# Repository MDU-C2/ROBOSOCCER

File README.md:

Multi-robot Soccer - RoboCup
=======================

About
-----------------------
Welcome to the DVA490 and DVA474 Project Course, project name Multi-robot Soccer - RoboCup. 
The project is about creating SSL RoboCup (Division B) robots and developing the accompanying software.

Roadmap
-----------------------
Hardware:
- [ ] Hardware mechanical design
- [ ] Hardware 3D design
- [ ] Hardware circuit/electrical design

Software:
- [x] Simulation Interface
- [x] SSL Interface
- [ ] Hardware Interface
- [ ] Communication protocol
- [ ] Raspberry Pi executable (Individual Robot Behaviour)
- [ ] Central computer executable (Collective Robot Behaviour)

Contributors and roles
-----------------------
This project was developed by:
- Mudar Ibrahim: Team leader and software developer
- Carl Larsson: Software lead and software developer
- Viktor Eriksson: Software developer
- Jacob Johansson: Software developer
- Aaiza Aziz Khan: Software developer
- Shruthi Puthiya Kunnon: Software developer
- Emil Åberg: Software developer
- Pontus Svensson: Hardware lead, hardware developer and software developer
- Anton Grusell: Hardware developer
- Johanna Melander: Hardware developer
- Fredrik Westerbom: Hardware developer and software developer

### Contact:
Carl Larsson: cln20001@student.mdu.se

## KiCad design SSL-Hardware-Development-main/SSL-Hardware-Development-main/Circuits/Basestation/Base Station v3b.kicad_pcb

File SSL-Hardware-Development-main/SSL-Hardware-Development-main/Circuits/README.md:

# Circuit Designs

This folder contains all circuitry and PCB design for the robot.

See [CONTRIBUTING.md](Documentation/CONTRIBUTING.md#Contributing-to-Hardware) 

## Changes
Update your changes here, include a description, file, name and commit number.

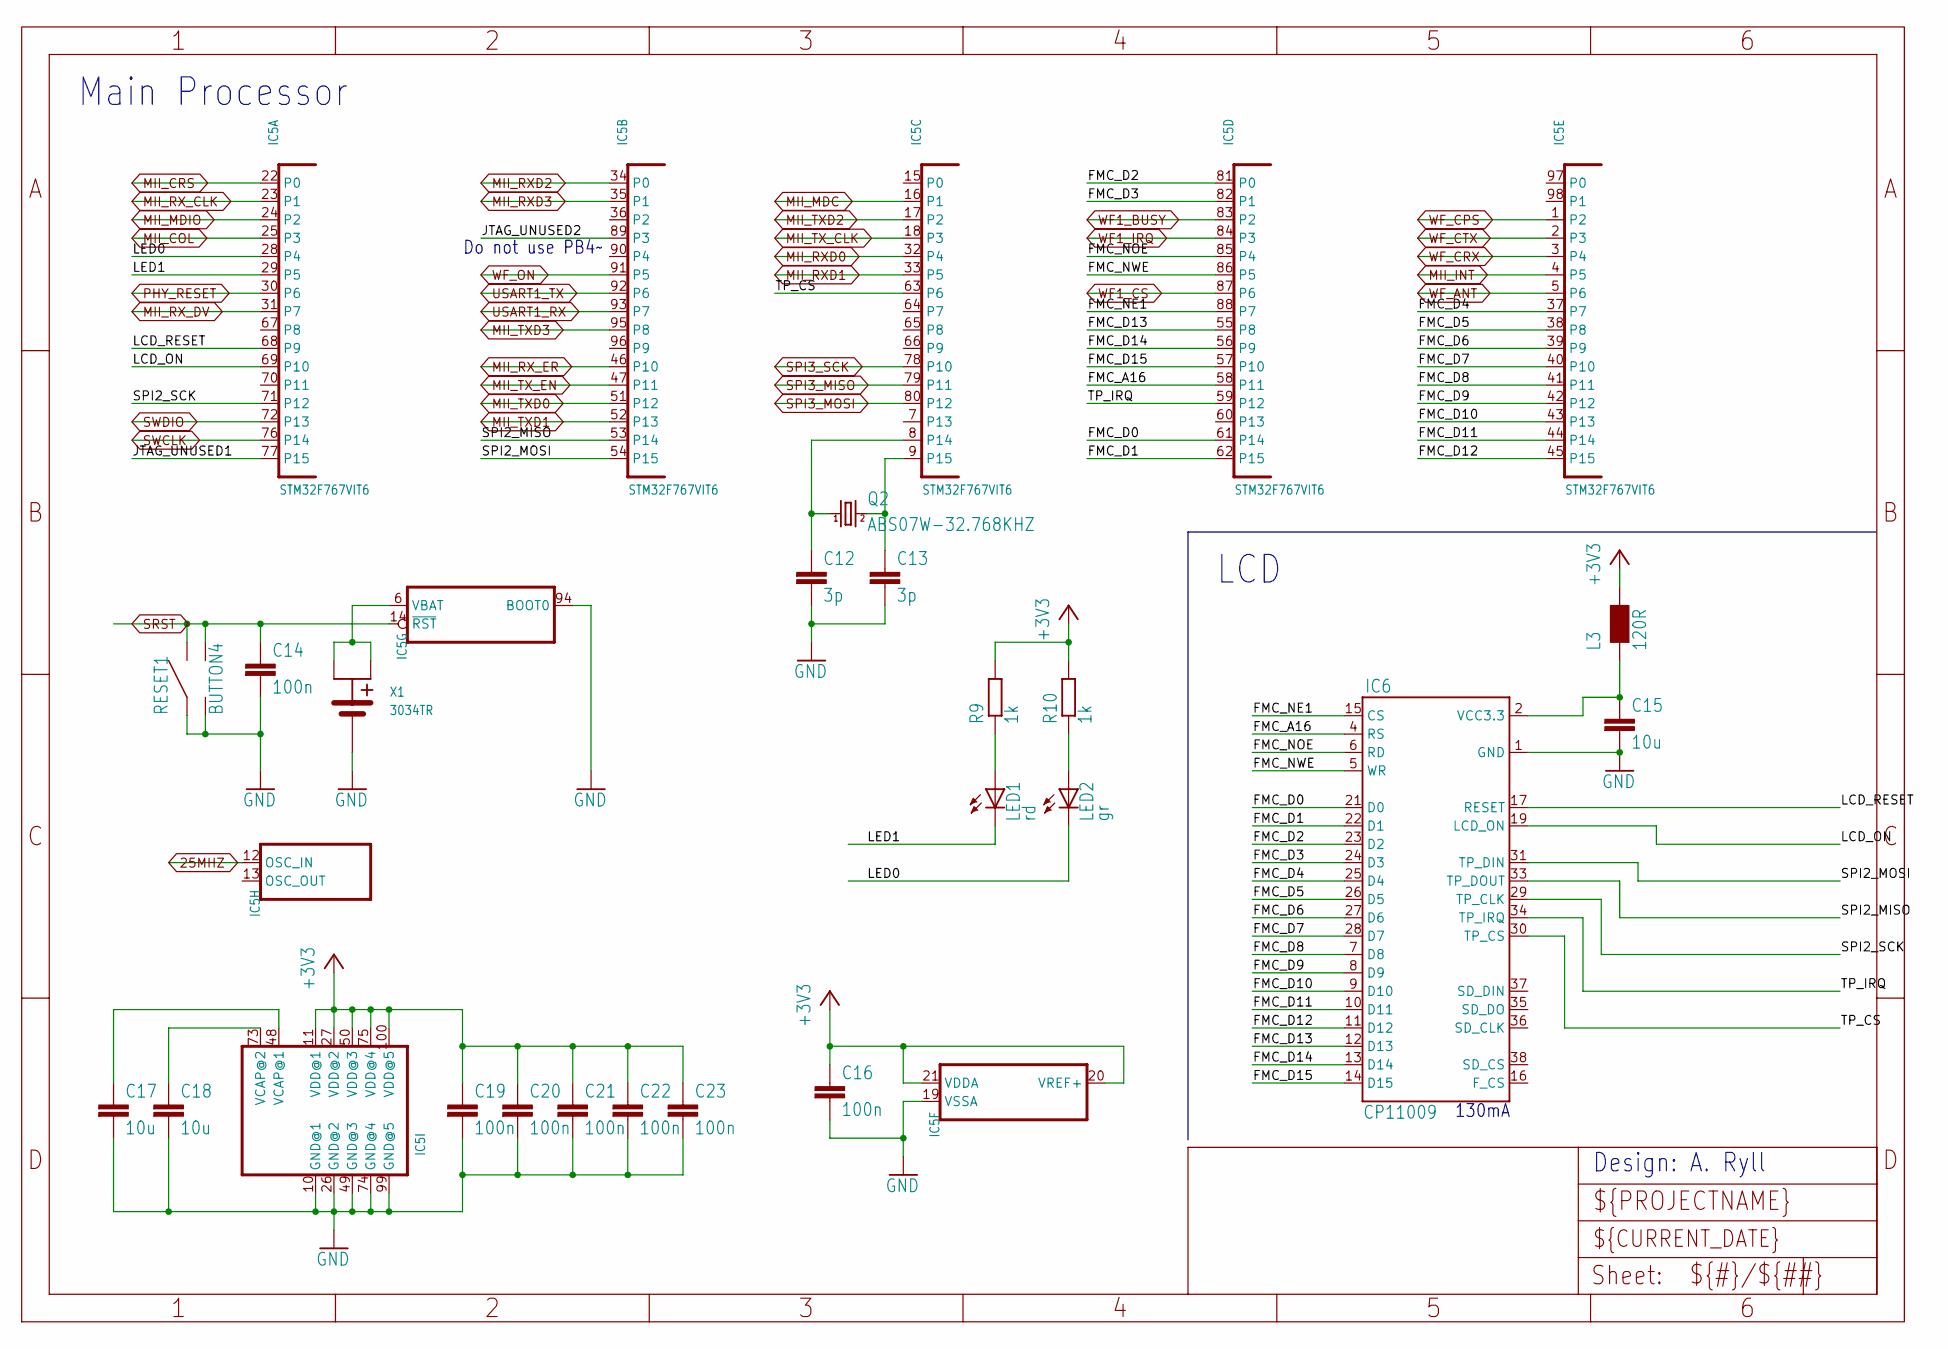
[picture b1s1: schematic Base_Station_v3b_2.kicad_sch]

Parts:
C12, C13: 3p; C0603
C14, C16, C19, C20, C21, C22, C23: 100n; C0603
C15, C17, C18: 10u; C0603
IC5: STM32F767VIT6; LQFP100-ST
IC6: CP11009; CP11009-THX
L3: 120R; 0603
LED1: rd; CHIP-LED0603
LED2: gr; CHIP-LED0603
Q2: ABS07W-32.768KHZ; CRYSTAL-07W
R9, R10: 1k; R0603
RESET1: BUTTON4
X1: 3034TR; CR2025

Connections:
25MHZ: IC5.12 (OSC_IN); also elsewhere on the board
+3V3: C16.1, C19.1, C20.1, C21.1, C22.1, C23.1, IC5.11 (VDD@1), IC5.20 (VREF+), IC5.21 (VDDA), IC5.27 (VDD@2), IC5.50 (VDD@3), IC5.75 (VDD@4), IC5.100 (VDD@5), L3.2, R9.2, R10.2; also elsewhere on the board
FMC_A16: IC5.58 (P11), IC6.4 (RS)
FMC_D0: IC5.61 (P14), IC6.21 (D0)
FMC_D1: IC5.62 (P15), IC6.22 (D1)
FMC_D2: IC5.81 (P0), IC6.23 (D2)
FMC_D3: IC5.82 (P1), IC6.24 (D3)
FMC_D4: IC5.37 (P7), IC6.25 (D4)
FMC_D5: IC5.38 (P8), IC6.26 (D5)
FMC_D6: IC5.39 (P9), IC6.27 (D6)
FMC_D7: IC5.40 (P10), IC6.28 (D7)
FMC_D8: IC5.41 (P11), IC6.7 (D8)
FMC_D9: IC5.42 (P12), IC6.8 (D9)
FMC_D10: IC5.43 (P13), IC6.9 (D10)
FMC_D11: IC5.44 (P14), IC6.10 (D11)
FMC_D12: IC5.45 (P15), IC6.11 (D12)
FMC_D13: IC5.55 (P8), IC6.12 (D13)
FMC_D14: IC5.56 (P9), IC6.13 (D14)
FMC_D15: IC5.57 (P10), IC6.14 (D15)
FMC_NE1: IC5.88 (P7), IC6.15 (CS)
FMC_NOE: IC5.85 (P4), IC6.6 (RD)
FMC_NWE: IC5.86 (P5), IC6.5 (WR)
GND: C12.2, C13.2, C14.2, C15.2, C16.2, C17.2, C18.2, C19.2, C20.2, C21.2, C22.2, C23.2, IC5.10 (GND@1), IC5.19 (VSSA), IC5.26 (GND@2), IC5.49 (GND@3), IC5.74 (GND@4), IC5.94 (BOOT0), IC5.99 (GND@5), IC6.1 (GND), RESET1.1, RESET1.2, X1.GND; also elsewhere on the board
JTAG_UNUSED1: IC5.77 (P15)
JTAG_UNUSED2: IC5.89 (P3)
LCD_ON: IC5.69 (P10), IC6.19 (LCD_ON)
LCD_RESET: IC5.68 (P9), IC6.17 (RESET)
LED0: IC5.28 (P4), LED2.C
LED1: IC5.29 (P5), LED1.C
MII_COL: IC5.25 (P3); also elsewhere on the board
MII_CRS: IC5.22 (P0); also elsewhere on the board
MII_INT: IC5.4 (P5); also elsewhere on the board
MII_MDC: IC5.16 (P1); also elsewhere on the board
MII_MDIO: IC5.24 (P2); also elsewhere on the board
MII_RXD0: IC5.32 (P4); also elsewhere on the board
MII_RXD1: IC5.33 (P5); also elsewhere on the board
MII_RXD2: IC5.34 (P0); also elsewhere on the board
MII_RXD3: IC5.35 (P1); also elsewhere on the board
MII_RX_CLK: IC5.23 (P1); also elsewhere on the board
MII_RX_DV: IC5.31 (P7); also elsewhere on the board
MII_RX_ER: IC5.46 (P10); also elsewhere on the board
MII_TXD0: IC5.51 (P12); also elsewhere on the board
MII_TXD1: IC5.52 (P13); also elsewhere on the board
MII_TXD2: IC5.17 (P2); also elsewhere on the board
MII_TXD3: IC5.95 (P8); also elsewhere on the board
MII_TX_CLK: IC5.18 (P3); also elsewhere on the board
MII_TX_EN: IC5.47 (P11); also elsewhere on the board
unnamed: C18.1, IC5.73 (VCAP@2)
unnamed: C17.1, IC5.48 (VCAP@1)
unnamed: LED2.A, R10.1
unnamed: LED1.A, R9.1
unnamed: C15.1, IC6.2 (VCC3.3), L3.1
OSC32_IN: C12.1, IC5.8 (P14), Q2.1
OSC32_OUT: C13.1, IC5.9 (P15), Q2.2
PHY_RESET: IC5.30 (P6); also elsewhere on the board
SPI2_MISO: IC5.53 (P14), IC6.33 (TP_DOUT)
SPI2_MOSI: IC5.54 (P15), IC6.31 (TP_DIN)
SPI2_SCK: IC5.71 (P12), IC6.29 (TP_CLK)
SPI3_MISO: IC5.79 (P11); also elsewhere on the board
SPI3_MOSI: IC5.80 (P12); also elsewhere on the board
SPI3_SCK: IC5.78 (P10); also elsewhere on the board
SRST: C14.1, IC5.14 (~RST), RESET1.3, RESET1.4; also elsewhere on the board
SWCLK: IC5.76 (P14); also elsewhere on the board
SWDIO: IC5.72 (P13); also elsewhere on the board
TP_CS: IC5.63 (P6), IC6.30 (TP_CS)
TP_IRQ: IC5.59 (P12), IC6.34 (TP_IRQ)
USART1_RX: IC5.93 (P7); also elsewhere on the board
USART1_TX: IC5.92 (P6); also elsewhere on the board
VBAT: IC5.6 (VBAT), X1.POS1, X1.POS2
WF1_BUSY: IC5.83 (P2); also elsewhere on the board
WF1_CS: IC5.87 (P6); also elsewhere on the board
WF1_IRQ: IC5.84 (P3); also elsewhere on the board
WF_ANT: IC5.5 (P6); also elsewhere on the board
WF_CPS: IC5.1 (P2); also elsewhere on the board
WF_CRX: IC5.3 (P4); also elsewhere on the board
WF_CTX: IC5.2 (P3); also elsewhere on the board
WF_ON: IC5.91 (P5); also elsewhere on the board

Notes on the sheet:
130mA
LCD
Main Processor
Design: A. Ryll
Do not use PB4~~{}

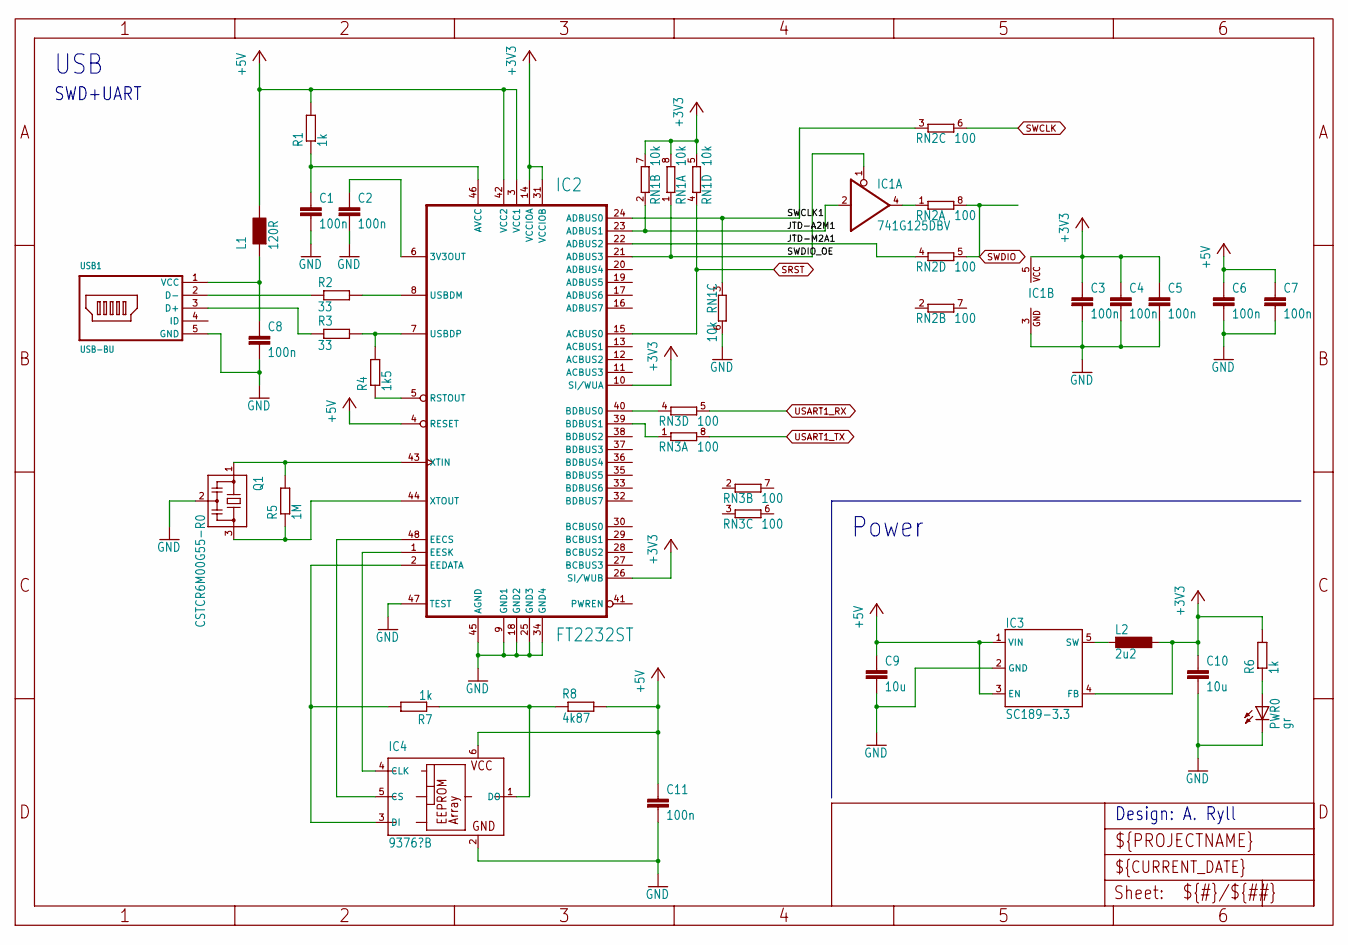
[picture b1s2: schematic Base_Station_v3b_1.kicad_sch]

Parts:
C1, C2, C3, C4, C5, C6, C7, C8, C11: 100n; C0603
C9, C10: 10u; C0603
IC1: 741G125DBV; SOT23-5
IC2: FT2232ST; LQFP48-ST
IC3: SC189-3.3; SOT23-5
IC4: 9376?B; SOT23-6
L1: 120R; 0603
L2: 2u2; IHLP1616
PWR0: gr; CHIP-LED0603
Q1: CSTCR6M00G55-R0; CSTCR6M
R1, R6, R7: 1k; R0603
R2, R3: 33; R0603
R4: 1k5; R0603
R5: 1M; R0603
R8: 4k87; R0603
RN1: 10k; EXB28V
RN2, RN3: 100; EXB28V
USB1: USB-BU; USB-BMICRO

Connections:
+3V3: C3.1, C4.1, C5.1, C10.1, IC1.5 (VCC), IC2.10 (SI/WUA), IC2.14 (VCCIOA), IC2.26 (SI/WUB), IC2.31 (VCCIOB), IC3.4 (FB), L2.P$1 (1), R6.2, RN1.5 (2), RN1.7 (2), RN1.8 (2); also elsewhere on the board
+5V: C6.1, C7.1, C9.1, C11.1, IC2.3 (VCC1), IC2.4 (RESET), IC2.42 (VCC2), IC3.1 (VIN), IC3.3 (EN), IC4.6 (VCC), L1.2, R1.2, R8.2; also elsewhere on the board
GND: C1.2, C2.2, C3.2, C4.2, C5.2, C6.2, C7.2, C8.2, C9.2, C10.2, C11.2, IC1.3 (GND), IC2.9 (GND1), IC2.18 (GND2), IC2.25 (GND3), IC2.34 (GND4), IC2.45 (AGND), IC2.47 (TEST), IC3.2 (GND), IC4.2 (GND), PWR0.C, Q1.2, RN1.6 (2), USB1.5 (GND); also elsewhere on the board
JTD-A2M1: IC1.2 (I), IC2.23 (ADBUS1), RN1.2 (1)
JTD-M2A1: IC2.22 (ADBUS2), RN2.4 (1)
unnamed: IC2.48 (EECS), IC4.5 (CS)
unnamed: IC2.1 (EESK), IC4.4 (CLK)
unnamed: IC2.2 (EEDATA), IC4.3 (DI), R7.2
unnamed: IC2.44 (XTOUT), Q1.3, R5.1
unnamed: IC4.1 (DO), R7.1, R8.1
unnamed: PWR0.A, R6.1
unnamed: IC1.4 (O), RN2.1
unnamed: IC2.40 (BDBUS0), RN3.4 (1)
unnamed: IC2.39 (BDBUS1), RN3.1
unnamed: IC2.7 (USBDP), R3.2, R4.2
unnamed: IC2.8 (USBDM), R2.2
unnamed: IC2.5 (RSTOUT), R4.1
unnamed: C2.1, IC2.6 (3V3OUT)
unnamed: C8.1, L1.1, USB1.1 (VCC)
unnamed: R2.1, USB1.2 (D-)
unnamed: R3.1, USB1.3 (D+)
unnamed: C1.1, IC2.46 (AVCC), R1.1
unnamed: IC2.43 (XTIN), Q1.1, R5.2
SRST: IC2.15 (ACBUS0), RN1.4 (1); also elsewhere on the board
SW-OUT: IC3.5 (SW), L2.P$2 (2)
SWCLK: RN2.6 (2); also elsewhere on the board
SWCLK1: IC2.24 (ADBUS0), RN1.3 (1), RN2.3 (1)
SWDIO: RN2.5 (2), RN2.8 (2); also elsewhere on the board
SWDIO_OE: IC1.1 (OE), IC2.21 (ADBUS3), RN1.1
USART1_RX: RN3.5 (2); also elsewhere on the board
USART1_TX: RN3.8 (2); also elsewhere on the board

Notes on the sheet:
Design: A. Ryll
USB
Power
SWD+UART

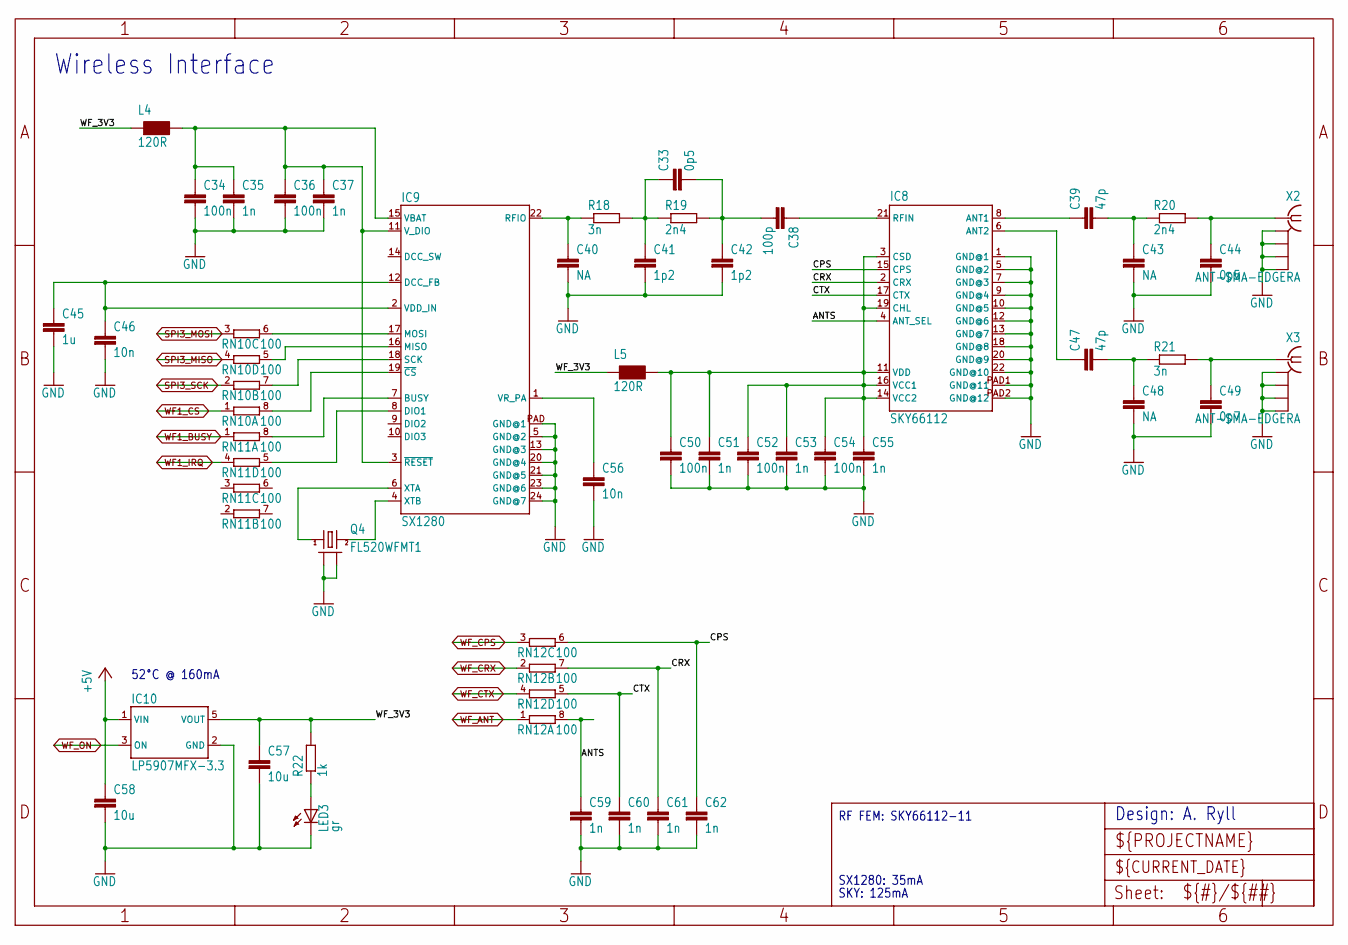
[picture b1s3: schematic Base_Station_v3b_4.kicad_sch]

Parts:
C33, C44: 0p5; C0402
C34, C36, C50, C52, C54: 100n; C0603
C35, C37, C51, C53, C55, C59, C60, C61, C62: 1n; C0603
C38: 100p; C0402
C39, C47: 47p; C0402
C40, C43, C48: NA; C0402
C41, C42: 1p2; C0402
C45: 1u; C0603
C46, C56: 10n; C0603
C49: 0p7; C0402
C57, C58: 10u; C0603
IC8: SKY66112; SMCM-22
IC9: SX1280; QFN24L
IC10: LP5907MFX-3.3; SOT23-5L
L4, L5: 120R; 0603
LED3: gr; CHIP-LED0603
Q4: FL520WFMT1; CRYSTAL-7M
R18, R21: 3n; R0402
R19, R20: 2n4; R0402
R22: 1k; R0603
RN10, RN11, RN12: 100; EXB28V
X2, X3: ANT-SMA-EDGERA; ANT-SMA-RA

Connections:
+5V: C58.1, IC10.1 (VIN); also elsewhere on the board
ANTS: C59.1, IC8.4 (ANT_SEL), RN12.8 (2)
CPS: C62.1, IC8.15 (CPS), RN12.6 (2)
CRX: C61.1, IC8.2 (CRX), RN12.7 (2)
CTX: C60.1, IC8.17 (CTX), RN12.5 (2)
GND: C34.2, C35.2, C36.2, C37.2, C40.2, C41.2, C42.2, C43.2, C44.2, C45.2, C46.2, C48.2, C49.2, C50.2, C51.2, C52.2, C53.2, C54.2, C55.2, C56.2, C57.2, C58.2, C59.2, C60.2, C61.2, C62.2, IC8.1 (GND@1), IC8.5 (GND@2), IC8.7 (GND@3), IC8.9 (GND@4), IC8.10 (GND@5), IC8.12 (GND@6), IC8.13 (GND@7), IC8.18 (GND@8), IC8.20 (GND@9), IC8.22 (GND@10), IC8.PAD1 (GND@11), IC8.PAD2 (GND@12), IC9.5 (GND@2), IC9.13 (GND@3), IC9.20 (GND@4), IC9.21 (GND@5), IC9.23 (GND@6), IC9.24 (GND@7), IC9.PAD (GND@1), IC10.2 (GND), LED3.C, Q4.2 (GND1), Q4.4 (GND2), X2.GND1 (GND), X2.GND2 (GND1), X2.GND3 (GND2), X2.GND4 (GND3), X3.GND1 (GND), X3.GND2 (GND1), X3.GND3 (GND2), X3.GND4 (GND3); also elsewhere on the board
unnamed: IC9.17 (MOSI), RN10.6 (2)
unnamed: IC9.16 (MISO), RN10.5 (2)
unnamed: IC9.18 (SCK), RN10.7 (2)
unnamed: IC9.19 (~CS), RN10.8 (2)
unnamed: IC9.7 (BUSY), RN11.8 (2)
unnamed: IC9.8 (DIO1), RN11.5 (2)
unnamed: LED3.A, R22.1
unnamed: IC9.6 (XTA), Q4.1
unnamed: IC9.4 (XTB), Q4.3 (2)
unnamed: C33.1, C41.1, R18.2, R19.1
unnamed: C33.2, C38.2, C42.1, R19.2
unnamed: C56.1, IC9.1 (VR_PA)
unnamed: C45.1, C46.1, IC9.2 (VDD_IN), IC9.12 (DCC_FB)
unnamed: C38.1, IC8.21 (RFIN)
unnamed: C39.2, C43.1, R20.1
unnamed: C44.1, R20.2, X2.C (1)
unnamed: C47.2, C48.1, R21.1
unnamed: C49.1, R21.2, X3.C (1)
unnamed: C39.1, IC8.8 (ANT1)
unnamed: C47.1, IC8.6 (ANT2)
RFIO1: C40.1, IC9.22 (RFIO), R18.1
SPI3_MISO: RN10.4 (1); also elsewhere on the board
SPI3_MOSI: RN10.3 (1); also elsewhere on the board
SPI3_SCK: RN10.2 (1); also elsewhere on the board
WF1_BUSY: RN11.1; also elsewhere on the board
WF1_CS: RN10.1; also elsewhere on the board
WF1_IRQ: RN11.4 (1); also elsewhere on the board
WF_3V3: C57.1, IC10.5 (VOUT), L4.1, L5.1, R22.2
WF_3V3FEM: C50.1, C51.1, C52.1, C53.1, C54.1, C55.1, IC8.3 (CSD), IC8.11 (VDD), IC8.14 (VCC2), IC8.16 (VCC1), IC8.19 (CHL), L5.2
WF_3V3SX: C34.1, C35.1, C36.1, C37.1, IC9.3 (~RESET), IC9.11 (V_DIO), IC9.15 (VBAT), L4.2
WF_ANT: RN12.1; also elsewhere on the board
WF_CPS: RN12.3 (1); also elsewhere on the board
WF_CRX: RN12.2 (1); also elsewhere on the board
WF_CTX: RN12.4 (1); also elsewhere on the board
WF_ON: IC10.3 (ON); also elsewhere on the board

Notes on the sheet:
SX1280: 35mA
52°C @ 160mA
Wireless Interface
RF FEM: SKY66112-11
SKY: 125mA
Design: A. Ryll

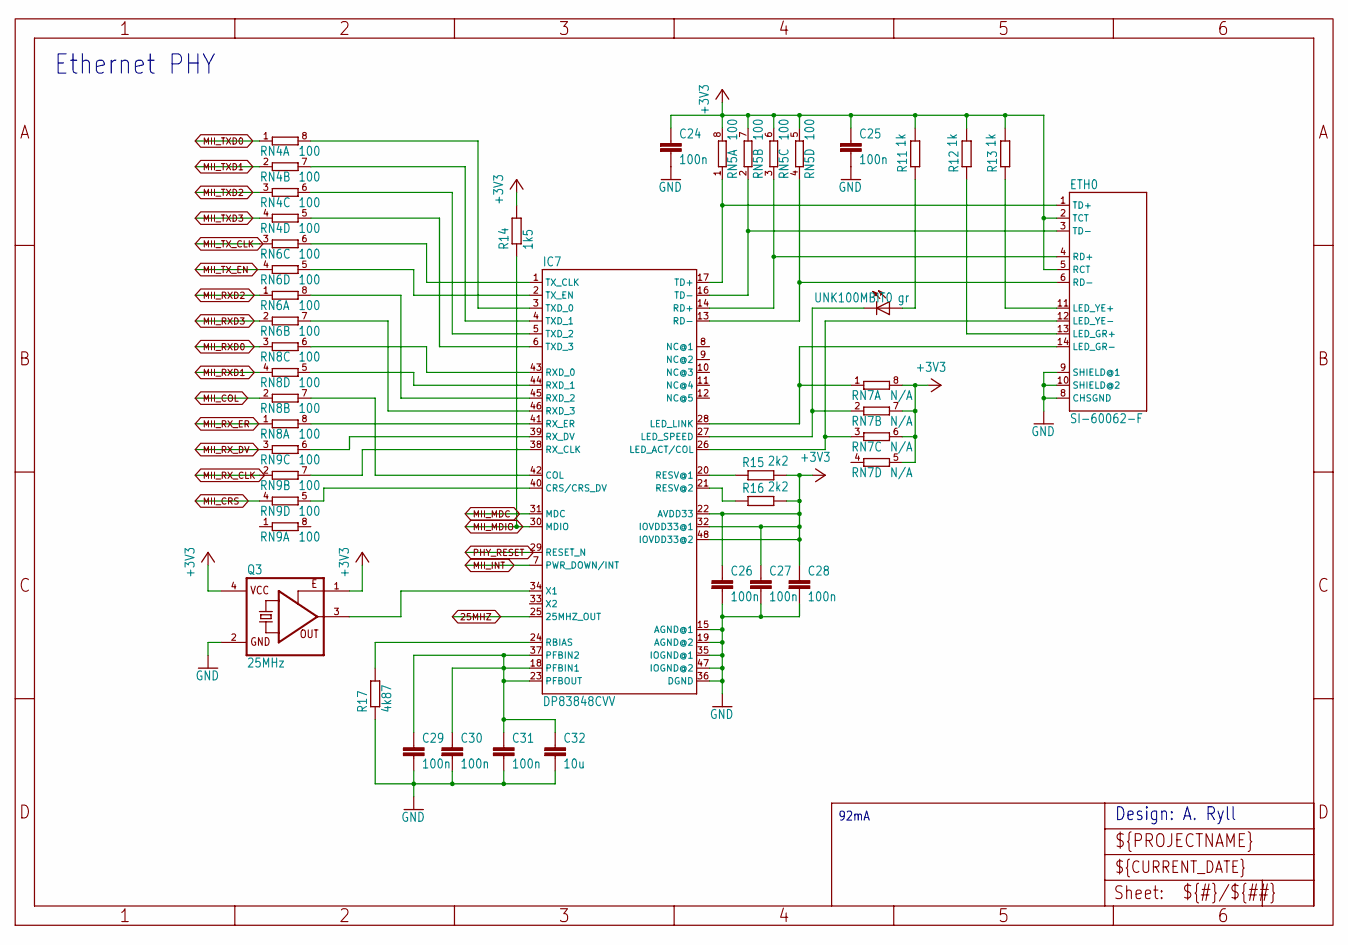
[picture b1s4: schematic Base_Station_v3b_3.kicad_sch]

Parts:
C24, C25, C26, C27, C28, C29, C30, C31: 100n; C0603
C32: 10u; C0603
ETH0: SI-60062-F; RJ45-LED
IC7: DP83848CVV; LQFP48
Q3: 25MHz; 7X
R11, R12, R13: 1k; R0603
R14: 1k5; R0603
R15, R16: 2k2; R0603
R17: 4k87; R0603
RN4, RN5, RN6, RN8, RN9: 100; EXB28V
RN7: N/A; EXB28V
UNK100MBIT0: gr; CHIP-LED0603

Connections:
25MHZ: IC7.25 (25MHZ_OUT); also elsewhere on the board
+3V3: C24.1, C25.1, C26.1, C27.1, C28.1, ETH0.2 (TCT), ETH0.5 (RCT), IC7.22 (AVDD33), IC7.32 (IOVDD33@1), IC7.48 (IOVDD33@2), Q3.1 (OE), Q3.4 (VCC), R11.2, R12.2, R13.2, R14.2, R15.2, R16.2, RN5.5 (2), RN5.6 (2), RN5.7 (2), RN5.8 (2), RN7.5 (2), RN7.6 (2), RN7.7 (2), RN7.8 (2); also elsewhere on the board
GND: C24.2, C25.2, C26.2, C27.2, C28.2, C29.2, C30.2, C31.2, C32.2, ETH0.8 (CHSGND), ETH0.9 (SHIELD@1), ETH0.10 (SHIELD@2), IC7.15 (AGND@1), IC7.19 (AGND@2), IC7.35 (IOGND@1), IC7.36 (DGND), IC7.47 (IOGND@2), Q3.2 (GND), R17.1; also elsewhere on the board
MII_COL: RN8.2 (1); also elsewhere on the board
MII_CRS: RN9.4 (1); also elsewhere on the board
MII_INT: IC7.7 (PWR_DOWN/INT); also elsewhere on the board
MII_MDC: IC7.31 (MDC); also elsewhere on the board
MII_MDIO: IC7.30 (MDIO), R14.1; also elsewhere on the board
MII_RXD0: RN8.3 (1); also elsewhere on the board
MII_RXD1: RN8.4 (1); also elsewhere on the board
MII_RXD2: RN6.1; also elsewhere on the board
MII_RXD3: RN6.2 (1); also elsewhere on the board
MII_RX_CLK: RN9.2 (1); also elsewhere on the board
MII_RX_DV: RN9.3 (1); also elsewhere on the board
MII_RX_ER: RN8.1; also elsewhere on the board
MII_TXD0: RN4.1; also elsewhere on the board
MII_TXD1: RN4.2 (1); also elsewhere on the board
MII_TXD2: RN4.3 (1); also elsewhere on the board
MII_TXD3: RN4.4 (1); also elsewhere on the board
MII_TX_CLK: RN6.3 (1); also elsewhere on the board
MII_TX_EN: RN6.4 (1); also elsewhere on the board
unnamed: IC7.3 (TXD_0), RN4.8 (2)
unnamed: IC7.4 (TXD_1), RN4.7 (2)
unnamed: IC7.5 (TXD_2), RN4.6 (2)
unnamed: IC7.6 (TXD_3), RN4.5 (2)
unnamed: IC7.1 (TX_CLK), RN6.6 (2)
unnamed: IC7.2 (TX_EN), RN6.5 (2)
unnamed: IC7.45 (RXD_2), RN6.8 (2)
unnamed: IC7.46 (RXD_3), RN6.7 (2)
unnamed: IC7.43 (RXD_0), RN8.6 (2)
unnamed: IC7.44 (RXD_1), RN8.5 (2)
unnamed: IC7.42 (COL), RN8.7 (2)
unnamed: IC7.41 (RX_ER), RN8.8 (2)
unnamed: IC7.39 (RX_DV), RN9.6 (2)
unnamed: IC7.38 (RX_CLK), RN9.7 (2)
unnamed: IC7.40 (CRS/CRS_DV), RN9.5 (2)
unnamed: IC7.24 (RBIAS), R17.2
unnamed: C29.1, C30.1, C31.1, C32.1, IC7.18 (PFBIN1), IC7.23 (PFBOUT), IC7.37 (PFBIN2)
unnamed: IC7.20 (RESV@1), R15.1
unnamed: IC7.21 (RESV@2), R16.1
unnamed: ETH0.12 (LED_YE-), IC7.26 (LED_ACT/COL), RN7.3 (1)
unnamed: IC7.27 (LED_SPEED), RN7.2 (1), UNK100MBIT0.C
unnamed: ETH0.14 (LED_GR-), IC7.28 (LED_LINK), RN7.1
unnamed: ETH0.6 (RD-), IC7.13 (RD-), RN5.4 (1)
unnamed: ETH0.4 (RD+), IC7.14 (RD+), RN5.3 (1)
unnamed: ETH0.3 (TD-), IC7.16 (TD-), RN5.2 (1)
unnamed: ETH0.1 (TD+), IC7.17 (TD+), RN5.1
unnamed: R11.1, UNK100MBIT0.A
unnamed: ETH0.13 (LED_GR+), R12.1
unnamed: ETH0.11 (LED_YE+), R13.1
unnamed: IC7.34 (X1), Q3.3 (FO)
PHY_RESET: IC7.29 (RESET_N); also elsewhere on the board

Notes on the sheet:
Ethernet PHY
92mA
Design: A. Ryll

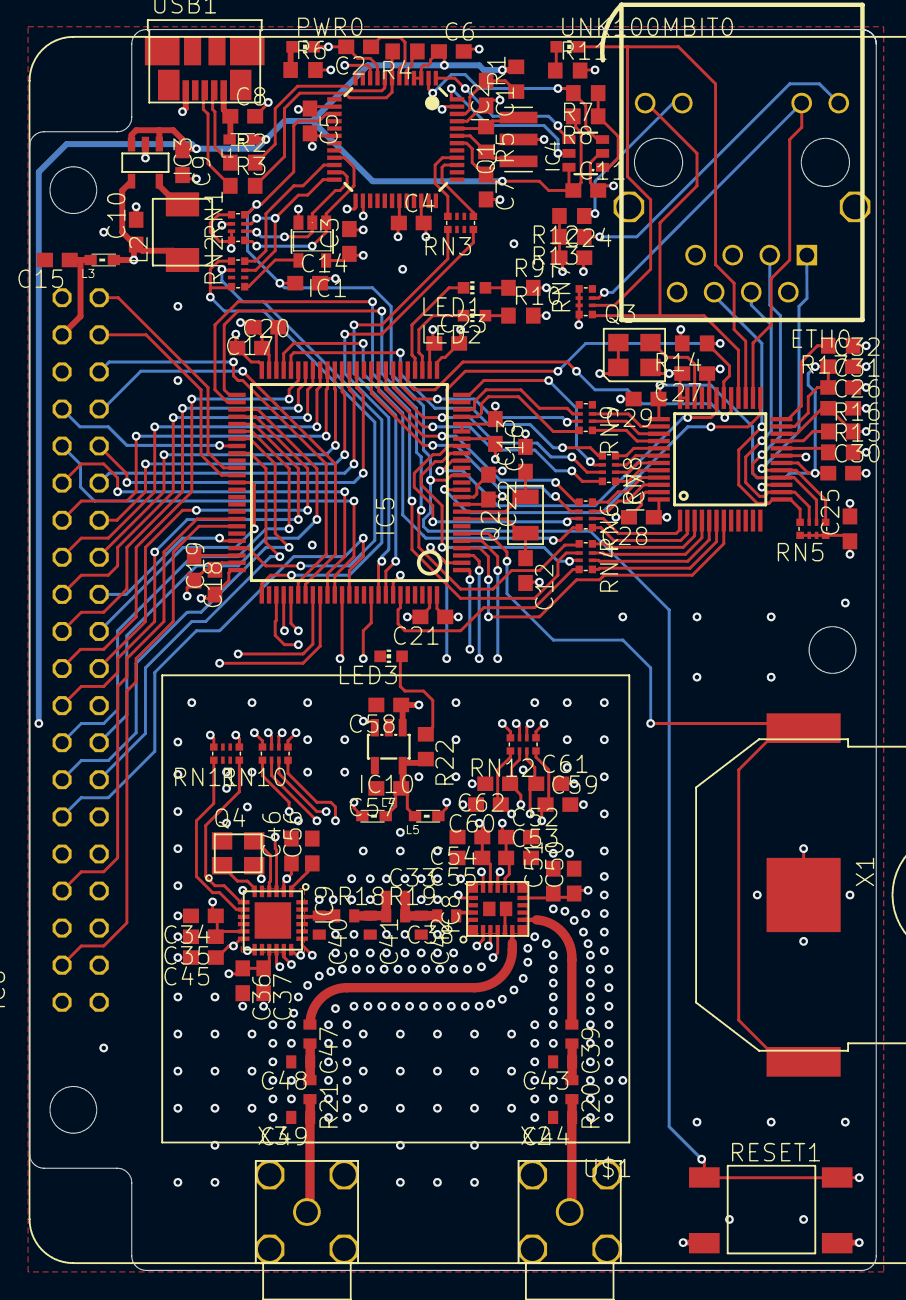
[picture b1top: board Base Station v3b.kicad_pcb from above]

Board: 4 copper layers, 58.0 x 85.0 mm, 130 parts (0 on the bottom side), 157 nets.

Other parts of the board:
@HOLE0, @HOLE1, @HOLE2: (no value)
U$1: BMI-S-204-F; SHIELD-32MM

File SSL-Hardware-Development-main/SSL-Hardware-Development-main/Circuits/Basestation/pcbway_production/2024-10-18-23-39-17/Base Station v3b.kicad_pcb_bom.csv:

Designator,Quantity,Value,Footprint,Package,MPN,DNP,Mount_Type
"@HOLE0, @HOLE1, @HOLE2",3,,,,,,tht
"C1, C11, C14, C16, C19, C2, C20, C21, C22, C23, C24, C25, C26, C27, C28, C29, C3, C30, C31, C34, C36, C4, C5, C50, C52, C54, C6, C7, C8",29,100n,C0603,,,,tht
"C10, C15, C17, C18, C32, C57, C58, C9",8,10u,C0603,,,,tht
"C12, C13",2,3p,C0603,,,,tht
"C33, C44",2,0p5,C0402,,,,tht
"C35, C37, C51, C53, C55, C59, C60, C61, C62",9,1n,C0603,,,,tht
C38,1,100p,C0402,,,,tht
"C39, C47",2,47p,C0402,,,,tht
"C40, C43, C48",3,NA,C0402,,,,tht
"C41, C42",2,1p2,C0402,,,,tht
C45,1,1u,C0603,,,,tht
"C46, C56",2,10n,C0603,,,,tht
C49,1,0p7,C0402,,,,tht
ETH0,1,SI-60062-F,RJ45-LED,,,,tht
IC1,1,74LVC1G125DBV,SOT23-5,,,,tht
IC10,1,LP5907MFX-3.3,SOT23-5L,,,,tht
IC2,1,FT2232ST,LQFP48-ST,,,,tht
IC3,1,SC189-3.3,SOT23-5,,,,tht
IC4,1,93C76B,SOT23-6,,,,tht
IC5,1,STM32F767VIT6,LQFP100-ST,,,,tht
IC6,1,CP11009,CP11009-THX,,,,tht
IC7,1,DP83848CVV,LQFP48,,,,tht
IC8,1,SKY66112,SMCM-22,,,,tht
IC9,1,SX1280,QFN24L,,,,tht
"L1, L3, L4, L5",4,120R,0603,,,,tht
L2,1,2u2,IHLP1616,,,,tht
LED1,1,rd,CHIP-LED0603,,,,tht
"LED2, LED3, PWR0, UNK100MBIT0",4,gr,CHIP-LED0603,,,,tht
Q1,1,CSTCR6M00G55-R0,CSTCR6M,,,,tht
Q2,1,ABS07W-32.768KHZ,CRYSTAL-07W,,,,tht
Q3,1,25MHz,7X,,,,tht
Q4,1,FL520WFMT1,CRYSTAL-7M,,,,tht
"R1, R10, R11, R12, R13, R22, R6, R7, R9",9,1k,R0603,,,,tht
"R14, R4",2,1k5,R0603,,,,tht
"R15, R16",2,2k2,R0603,,,,tht
"R17, R8",2,4k87,R0603,,,,tht
"R18, R21",2,3n,R0402,,,,tht
"R19, R20",2,2n4,R0402,,,,tht
"R2, R3",2,33,R0603,,,,tht
R5,1,1M,R0603,,,,tht
RESET1,1,BUTTON4,BUTTON4,,,,tht
RN1,1,10k,EXB28V,,,,tht
"RN10, RN11, RN12, RN2, RN3, RN4, RN5, RN6, RN8, RN9",10,100,EXB28V,,,,tht
RN7,1,N/A,EXB28V,,,,tht
U$1,1,BMI-S-204-F,SHIELD-32MM,,,,tht
USB1,1,USB-BU,USB-BMICRO,,,,tht
X1,1,3034TR ,CR2025,,,,tht
"X2, X3",2,,ANT-SMA-RA,,,,tht
